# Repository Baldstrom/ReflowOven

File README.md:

# ReflowOven
A reflow oven controller designed in KiCAD, by Jaden Bottemiller

This project is designed to use an STM32 ARM Cortex-M4 microcontroller. 

All onboard devices interface to the microcontroller using I2C (with the exception of the SD Card Slot, which uses SPI). Also has a CAN interface, USB 2.0, and SWD. Features four seven segment displays, three buttons, and a rotary encoder with a custom logic circuit that interfaces with an I2C binary up/down counter to increment, decrement, and maintain accuracy of the relative position of the encoder.

Here is a rendering of the board with all of the parts modelled.
Some models from online resources or default in KiCAD, but many were made by me in Solidworks.

The user interface portion of the board is able to be cut off so that it can be placed anywhere in a mechanical chassis for ease of construction.

Here is the board as seen by default in the KiCAD PCBnew Software.

A PDF of the Schematic Sheets can be found [here](https://github.com/Baldstrom/ReflowOven/blob/main/PDFs/ReflowOven.pdf).

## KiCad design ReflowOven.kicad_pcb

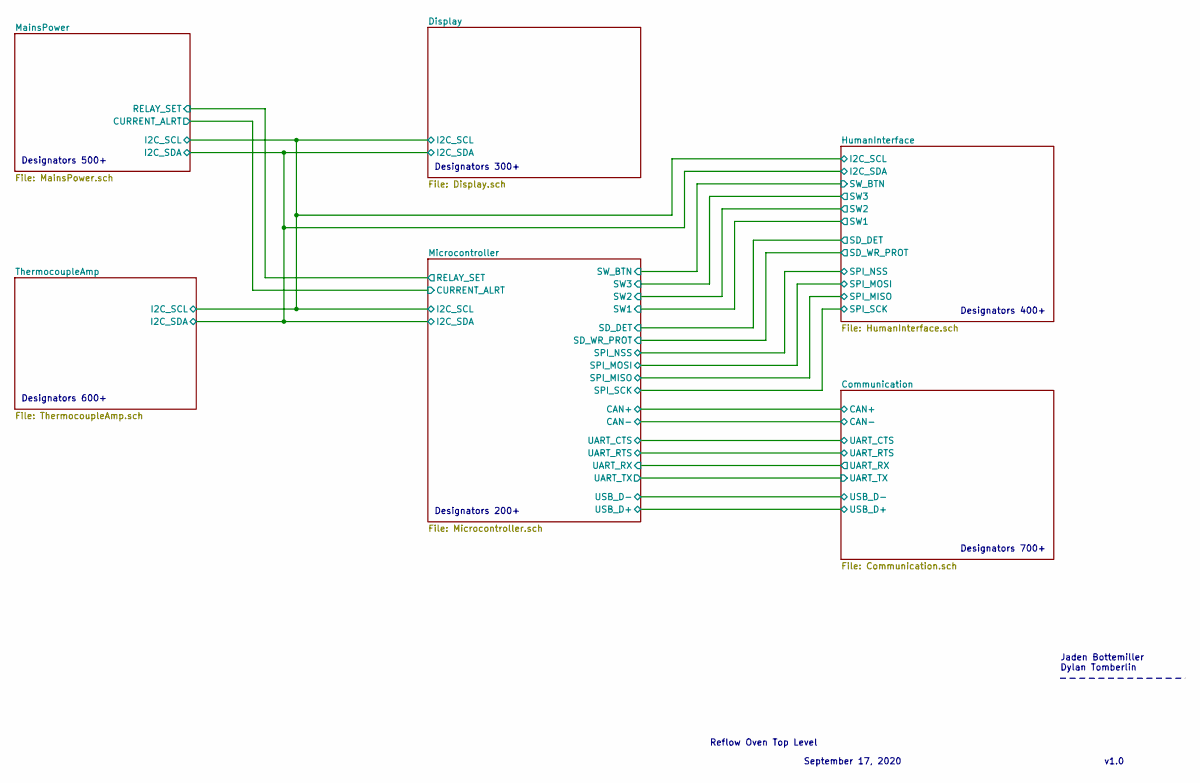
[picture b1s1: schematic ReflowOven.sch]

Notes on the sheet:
Reflow Oven Top Level
v1.0
September 17, 2020
Jaden Bottemiller Dylan Tomberlin
Designators 200+
Designators 600+
Designators 500+
Designators 300+
Designators 400+
Designators 700+

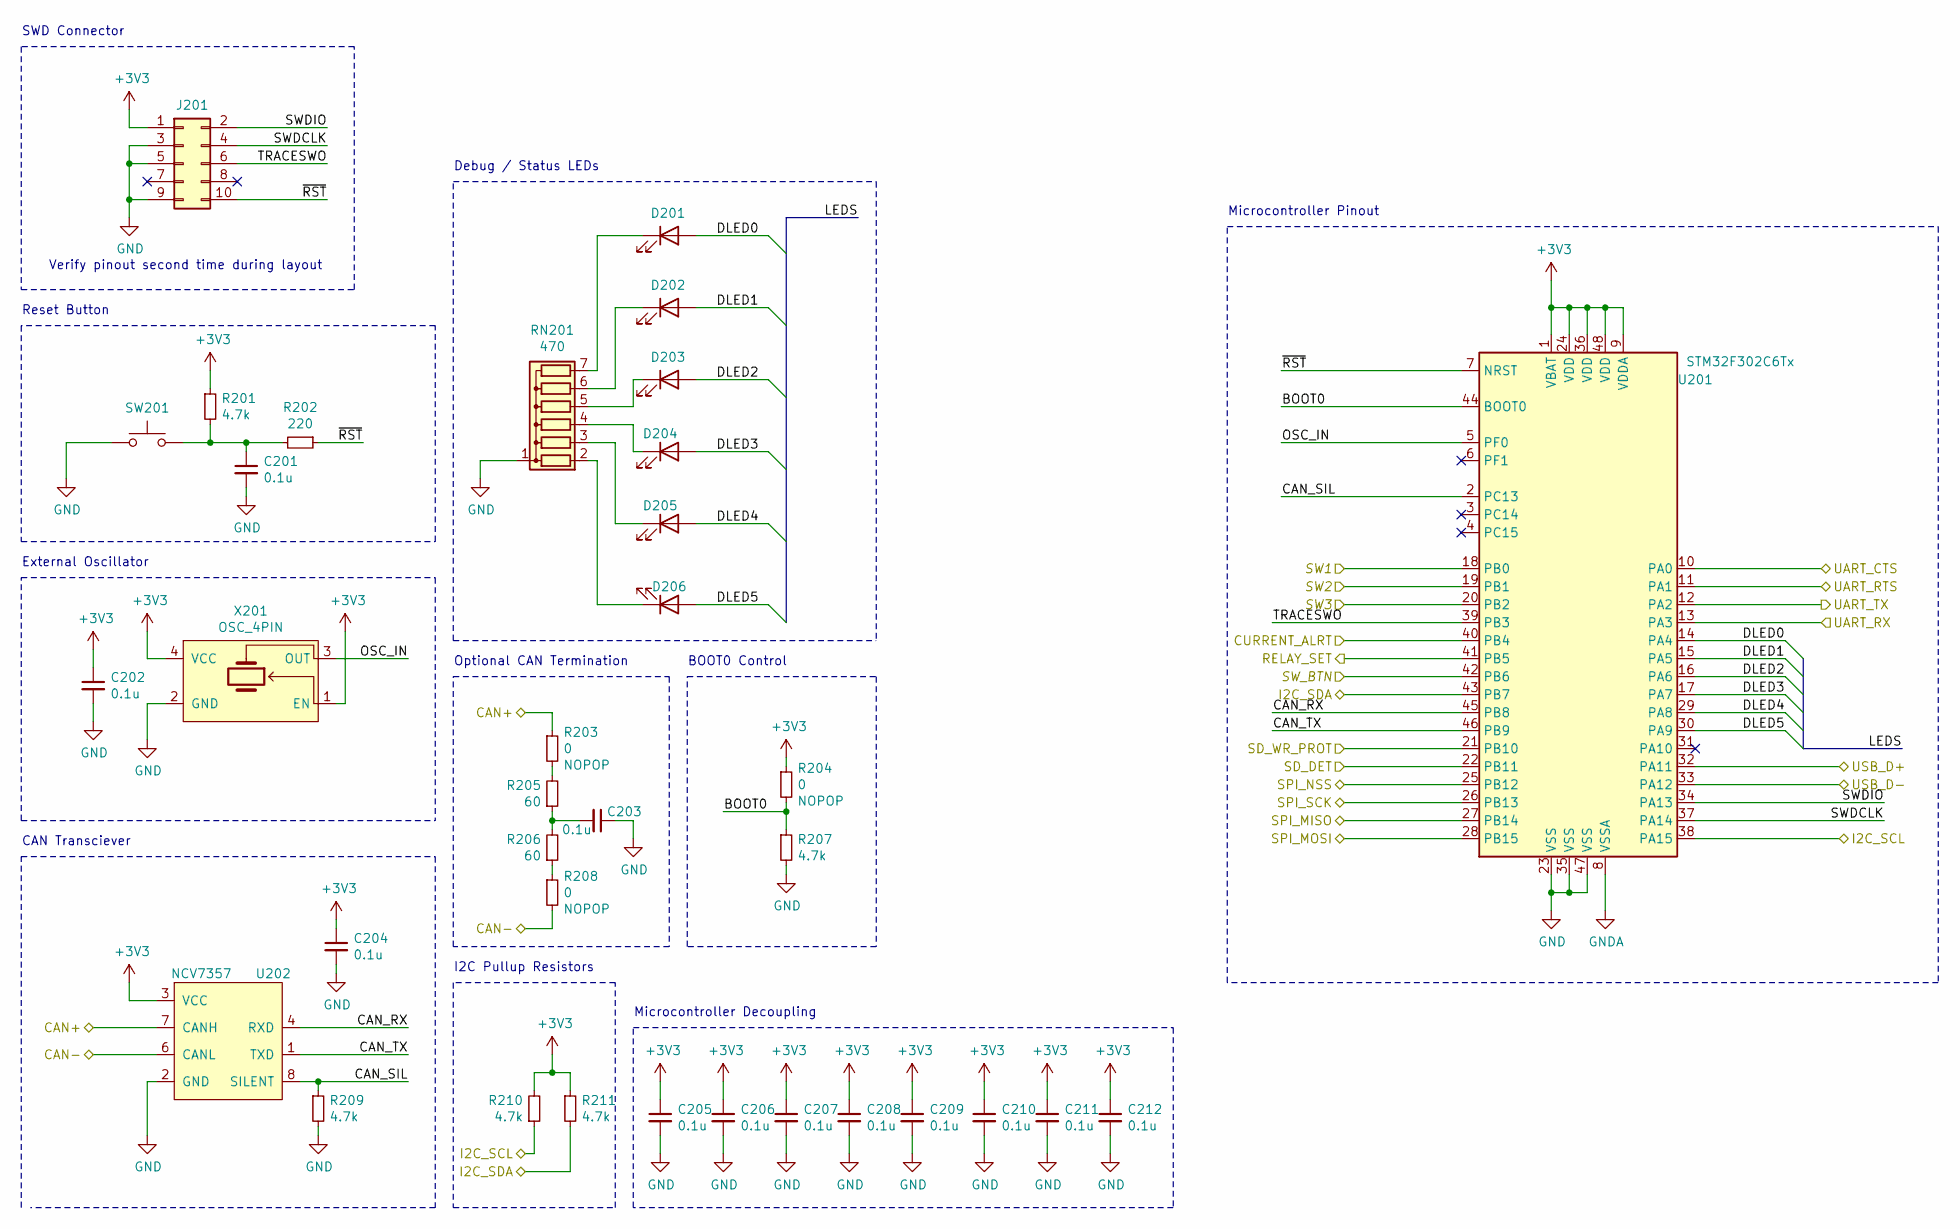
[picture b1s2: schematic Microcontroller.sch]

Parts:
C201, C202, C203, C204, C205, C206, C207, C208, C209, C210, C211, C212: 0.1u; C_0603_1608Metric
D201, D202, D203, D204, D205, D206: LED; LED_0603_1608Metric
J201: Conn_02x05_Odd_Even; CNC_3221-10-0100-00
R201, R207, R209, R210, R211: 4.7k; R_0603_1608Metric
R202: 220; R_0603_1608Metric
R203, R204, R208: 0; R_0201_0603Metric
R205, R206: 60; R_0603_1608Metric
RN201: 470; R_Array_SIP7
SW201: B3U-1100P; SW_B3U-1100P
U201: STM32F302C6Tx; LQFP-48_7x7mm_P0.5mm
U202: NCV7357; SOIC-8_3.9x4.9mm_P1.27mm
X201: OSC_4PIN; KC2016Z48.0000C15XXK

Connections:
/Communication/CAN+: R203.1, U202.7 (CANH); also elsewhere on the board
/Communication/CAN-: R208.2, U202.6 (CANL); also elsewhere on the board
/Communication/UART_CTS: U201.10 (PA0); also elsewhere on the board
/Communication/UART_RTS: U201.11 (PA1); also elsewhere on the board
/Communication/UART_RX: U201.13 (PA3); also elsewhere on the board
/Communication/UART_TX: U201.12 (PA2); also elsewhere on the board
/Communication/USB_D+: U201.32 (PA11); also elsewhere on the board
/Communication/USB_D-: U201.33 (PA12); also elsewhere on the board
/Display/I2C_SCL: R210.1, U201.38 (PA15); also elsewhere on the board
/Display/I2C_SDA: R211.2, U201.43 (PB7); also elsewhere on the board
/HumanInterface/SD_DET: U201.22 (PB11); also elsewhere on the board
/HumanInterface/SD_WR_PROT: U201.21 (PB10); also elsewhere on the board
/HumanInterface/SPI_MISO: U201.27 (PB14); also elsewhere on the board
/HumanInterface/SPI_MOSI: U201.28 (PB15); also elsewhere on the board
/HumanInterface/SPI_NSS: U201.25 (PB12); also elsewhere on the board
/HumanInterface/SPI_SCK: U201.26 (PB13); also elsewhere on the board
/HumanInterface/SW1: U201.18 (PB0); also elsewhere on the board
/HumanInterface/SW2: U201.19 (PB1); also elsewhere on the board
/HumanInterface/SW3: U201.20 (PB2); also elsewhere on the board
/HumanInterface/SW_BTN: U201.42 (PB6); also elsewhere on the board
/MainsPower/CURRENT_ALRT: U201.40 (PB4); also elsewhere on the board
/MainsPower/RELAY_SET: U201.41 (PB5); also elsewhere on the board
/Microcontroller/BOOT0: R204.2, R207.1, U201.44 (BOOT0)
/Microcontroller/CAN_RX: U201.45 (PB8), U202.4 (RXD)
/Microcontroller/CAN_SIL: R209.1, U201.2 (PC13), U202.8 (SILENT)
/Microcontroller/CAN_TX: U201.46 (PB9), U202.1 (TXD)
/Microcontroller/DLED0: D201.2 (A), U201.14 (PA4)
/Microcontroller/DLED1: D202.2 (A), U201.15 (PA5)
/Microcontroller/DLED2: D203.2 (A), U201.16 (PA6)
/Microcontroller/DLED3: D204.2 (A), U201.17 (PA7)
/Microcontroller/DLED4: D205.2 (A), U201.29 (PA8)
/Microcontroller/DLED5: D206.2 (A), U201.30 (PA9)
/Microcontroller/OSC_IN: U201.5 (PF0), X201.3 (OUT)
/Microcontroller/SWDCLK: J201.4, U201.37 (PA14)
/Microcontroller/SWDIO: J201.2, U201.34 (PA13)
/Microcontroller/TRACESWO: J201.6, U201.39 (PB3)
/Microcontroller/~RST: J201.10, R202.1, U201.7 (NRST)
GND: C201.2, C202.2, C203.1, C204.2, C205.2, C206.2, C207.2, C208.2, C209.2, C210.2, C211.2, C212.2, J201.3, J201.5, J201.9, R207.2, R209.2, RN201.1 (common), SW201.1, U201.8 (VSSA), U201.23 (VSS), U201.35 (VSS), U201.47 (VSS), U202.2 (GND), X201.2 (GND); also elsewhere on the board
unnamed: C201.1, R201.2, R202.2, SW201.2
unnamed: C203.2, R205.1, R206.2
unnamed: D201.1 (K), RN201.7 (R6)
unnamed: D202.1 (K), RN201.6 (R5)
unnamed: D203.1 (K), RN201.5 (R4)
unnamed: D204.1 (K), RN201.4 (R3)
unnamed: D205.1 (K), RN201.3 (R2)
unnamed: D206.1 (K), RN201.2 (R1)
unnamed: R203.2, R205.2
unnamed: R206.1, R208.1

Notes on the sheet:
Microcontroller Decoupling
Microcontroller Pinout
CAN Transciever
I2C Pullup Resistors
External Oscillator
Verify pinout second time during layout
SWD Connector
Reset Button
BOOT0 Control
Optional CAN Termination
Debug / Status LEDs

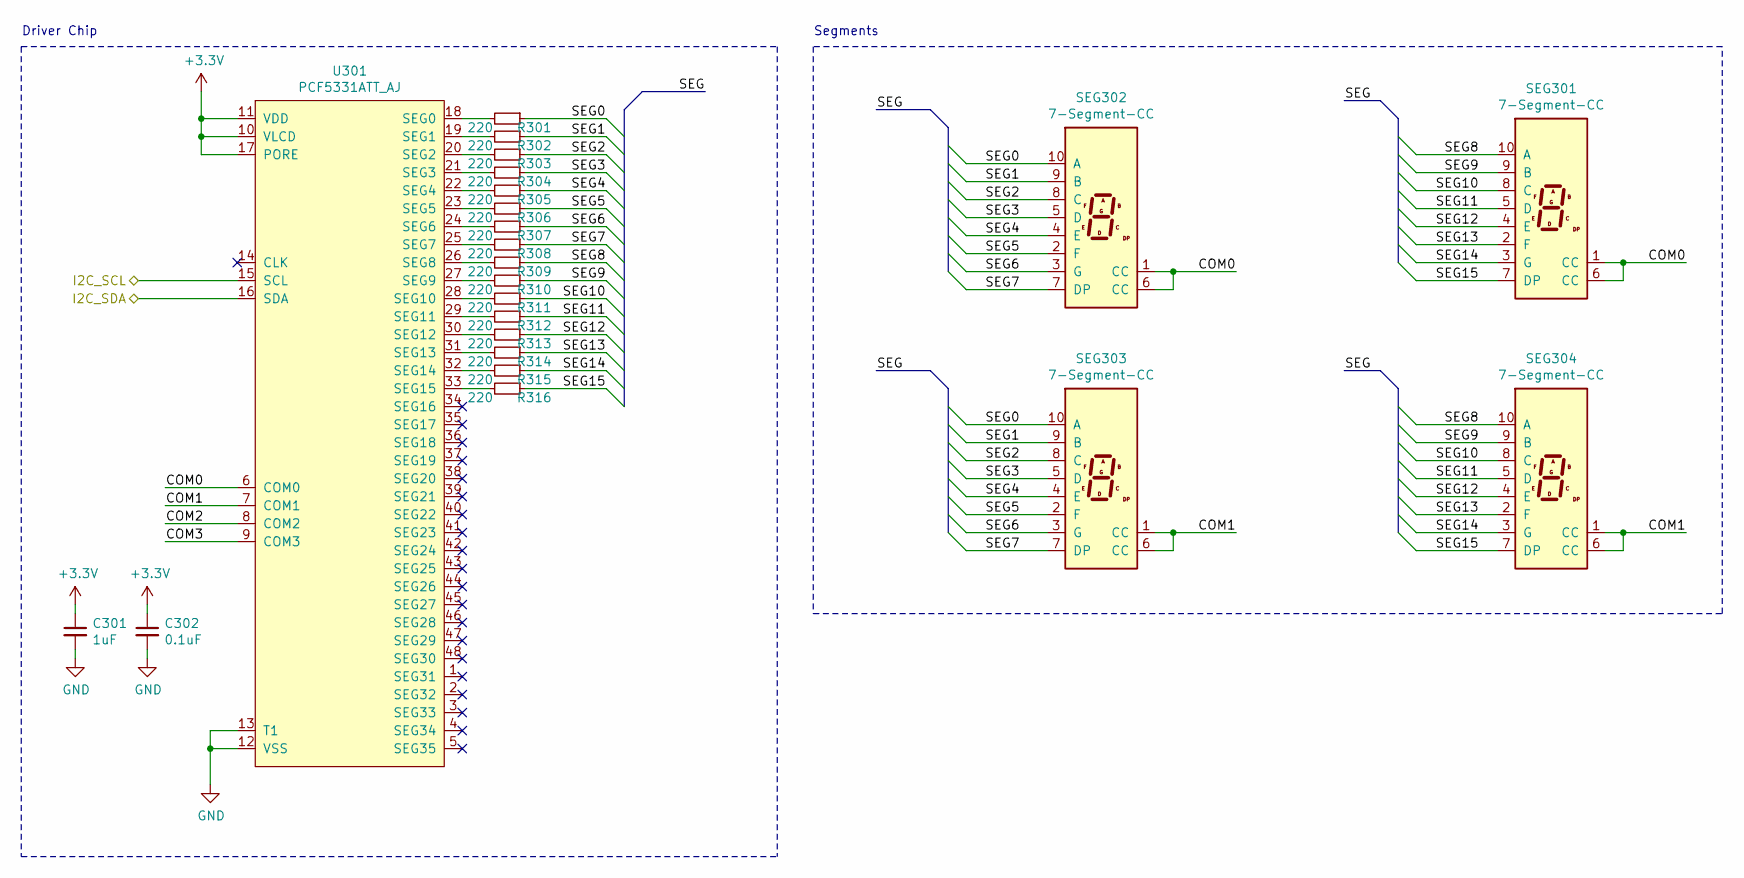
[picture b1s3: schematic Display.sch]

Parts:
C301: 1uF; C_0603_1608Metric
C302: 0.1uF; C_0603_1608Metric
R301, R302, R303, R304, R305, R306, R307, R308, R309, R310, R311, R312, R313, R314, R315, R316: 220; R_0603_1608Metric
SEG301, SEG302, SEG303, SEG304: 7-Segment-CC; Sx39-1xxxxx
U301: PCF5331ATT_AJ; TSSOP-48_6.1x12.5mm_P0.5mm

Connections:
/Display/COM0: SEG301.1 (CC), SEG301.6 (CC), SEG302.1 (CC), SEG302.6 (CC), U301.6 (COM0)
/Display/COM1: SEG303.1 (CC), SEG303.6 (CC), SEG304.1 (CC), SEG304.6 (CC), U301.7 (COM1)
/Display/COM2: U301.8 (COM2)
/Display/COM3: U301.9 (COM3)
/Display/I2C_SCL: U301.15 (SCL); also elsewhere on the board
/Display/I2C_SDA: U301.16 (SDA); also elsewhere on the board
/Display/SEG0: R301.1, SEG302.10 (A), SEG303.10 (A)
/Display/SEG1: R302.1, SEG302.9 (B), SEG303.9 (B)
/Display/SEG2: R303.1, SEG302.8 (C), SEG303.8 (C)
/Display/SEG3: R304.1, SEG302.5 (D), SEG303.5 (D)
/Display/SEG4: R305.1, SEG302.4 (E), SEG303.4 (E)
/Display/SEG5: R306.1, SEG302.2 (F), SEG303.2 (F)
/Display/SEG6: R307.1, SEG302.3 (G), SEG303.3 (G)
/Display/SEG7: R308.1, SEG302.7 (DP), SEG303.7 (DP)
/Display/SEG8: R309.1, SEG301.10 (A), SEG304.10 (A)
/Display/SEG9: R310.1, SEG301.9 (B), SEG304.9 (B)
/Display/SEG10: R311.1, SEG301.8 (C), SEG304.8 (C)
/Display/SEG11: R312.1, SEG301.5 (D), SEG304.5 (D)
/Display/SEG12: R313.1, SEG301.4 (E), SEG304.4 (E)
/Display/SEG13: R314.1, SEG301.2 (F), SEG304.2 (F)
/Display/SEG14: R315.1, SEG301.3 (G), SEG304.3 (G)
/Display/SEG15: R316.1, SEG301.7 (DP), SEG304.7 (DP)
GND: C301.2, C302.2, U301.12 (VSS), U301.13 (T1); also elsewhere on the board
unnamed: R301.2, U301.18 (SEG0)
unnamed: R302.2, U301.19 (SEG1)
unnamed: R303.2, U301.20 (SEG2)
unnamed: R304.2, U301.21 (SEG3)
unnamed: R305.2, U301.22 (SEG4)
unnamed: R306.2, U301.23 (SEG5)
unnamed: R307.2, U301.24 (SEG6)
unnamed: R308.2, U301.25 (SEG7)
unnamed: R309.2, U301.26 (SEG8)
unnamed: R310.2, U301.27 (SEG9)
unnamed: R311.2, U301.28 (SEG10)
unnamed: R312.2, U301.29 (SEG11)
unnamed: R313.2, U301.30 (SEG12)
unnamed: R314.2, U301.31 (SEG13)
unnamed: R315.2, U301.32 (SEG14)
unnamed: R316.2, U301.33 (SEG15)

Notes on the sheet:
Driver Chip
Segments

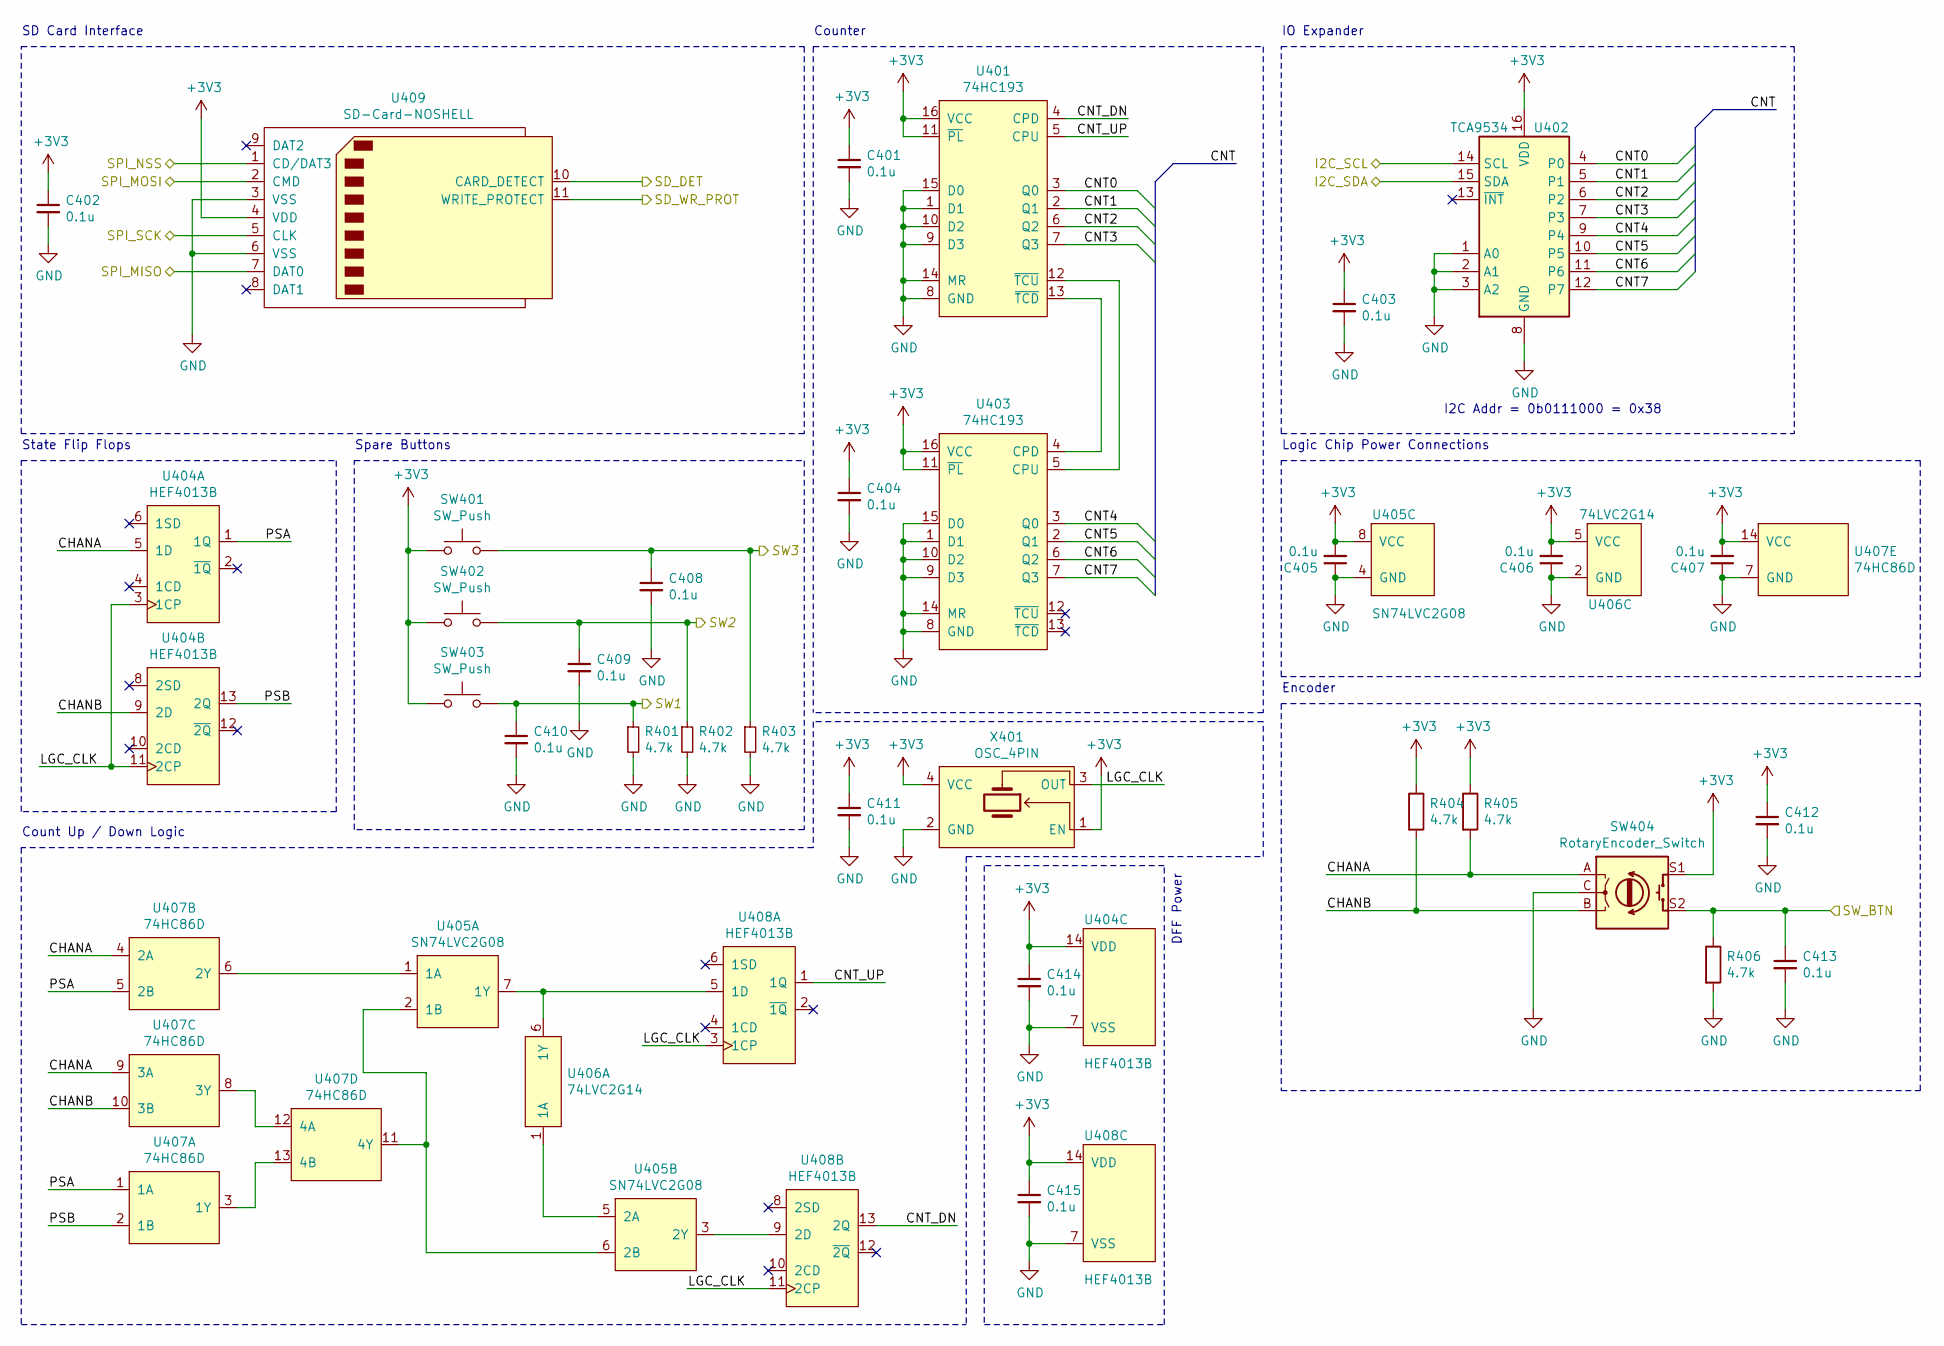
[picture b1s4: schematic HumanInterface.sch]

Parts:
C401, C402, C403, C404, C405, C406, C407, C408, C409, C410, C411, C412, C413, C414, C415: 0.1u; C_0603_1608Metric
R401, R402, R403, R404, R405, R406: 4.7k; R_0603_1608Metric
SW401, SW402, SW403: SW_Push; SW_KS11R21CQD
SW404: RotaryEncoder_Switch; EN12-HS22AF20
U401, U403: 74HC193; SOIC-16_3.9x9.9mm_P1.27mm
U402: TCA9534; TSSOP-16_4.4x5mm_P0.65mm
U404, U408: HEF4013B; SOIC-14_3.9x8.7mm_P1.27mm
U405: SN74LVC2G08; VSSOP-8_2.3x2mm_P0.5mm
U406: 74LVC2G14; TSOP-6_1.65x3.05mm_P0.95mm
U407: 74HC86D; SOIC-14_3.9x8.7mm_P1.27mm
U409: SD-Card-NOSHELL; AMPHENOL-10067847
X401: OSC_4PIN; KC2016Z48.0000C15XXK

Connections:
/Display/I2C_SCL: U402.14 (SCL); also elsewhere on the board
/Display/I2C_SDA: U402.15 (SDA); also elsewhere on the board
/HumanInterface/CHANA: R405.2, SW404.A, U404.5 (1D), U407.4 (2A), U407.9 (3A)
/HumanInterface/CHANB: R404.2, SW404.B, U404.9 (2D), U407.10 (3B)
/HumanInterface/CNT0: U401.3 (Q0), U402.4 (P0)
/HumanInterface/CNT1: U401.2 (Q1), U402.5 (P1)
/HumanInterface/CNT2: U401.6 (Q2), U402.6 (P2)
/HumanInterface/CNT3: U401.7 (Q3), U402.7 (P3)
/HumanInterface/CNT4: U402.9 (P4), U403.3 (Q0)
/HumanInterface/CNT5: U402.10 (P5), U403.2 (Q1)
/HumanInterface/CNT6: U402.11 (P6), U403.6 (Q2)
/HumanInterface/CNT7: U402.12 (P7), U403.7 (Q3)
/HumanInterface/CNT_DN: U401.4 (CPD), U408.13 (2Q)
/HumanInterface/CNT_UP: U401.5 (CPU), U408.1 (1Q)
/HumanInterface/LGC_CLK: U404.3 (1CP), U404.11 (2CP), U408.3 (1CP), U408.11 (2CP), X401.3 (OUT)
/HumanInterface/PSA: U404.1 (1Q), U407.1 (1A), U407.5 (2B)
/HumanInterface/PSB: U404.13 (2Q), U407.2 (1B)
/HumanInterface/SD_DET: U409.10 (CARD_DETECT); also elsewhere on the board
/HumanInterface/SD_WR_PROT: U409.11 (WRITE_PROTECT); also elsewhere on the board
/HumanInterface/SPI_MISO: U409.7 (DAT0); also elsewhere on the board
/HumanInterface/SPI_MOSI: U409.2 (CMD); also elsewhere on the board
/HumanInterface/SPI_NSS: U409.1 (CD/DAT3); also elsewhere on the board
/HumanInterface/SPI_SCK: U409.5 (CLK); also elsewhere on the board
/HumanInterface/SW1: C410.1, R401.1, SW403.2; also elsewhere on the board
/HumanInterface/SW2: C409.1, R402.1, SW402.2; also elsewhere on the board
/HumanInterface/SW3: C408.1, R403.1, SW401.2; also elsewhere on the board
/HumanInterface/SW_BTN: C413.1, R406.1, SW404.S2; also elsewhere on the board
GND: C401.2, C402.2, C403.2, C404.2, C405.1, C406.1, C407.1, C408.2, C409.2, C410.2, C411.2, C412.2, C413.2, C414.2, C415.2, R401.2, R402.2, R403.2, R406.2, SW404.C, U401.1 (D1), U401.8 (GND), U401.9 (D3), U401.10 (D2), U401.14 (MR), U401.15 (D0), U402.1 (A0), U402.2 (A1), U402.3 (A2), U402.8 (GND), U403.1 (D1), U403.8 (GND), U403.9 (D3), U403.10 (D2), U403.14 (MR), U403.15 (D0), U404.7 (VSS), U405.4 (GND), U406.2 (GND), U407.7 (GND), U408.7 (VSS), U409.3 (VSS), U409.6 (VSS), U409.GND, X401.2 (GND); also elsewhere on the board
unnamed: U401.12 (~TCU), U403.5 (CPU)
unnamed: U401.13 (~TCD), U403.4 (CPD)
unnamed: U405.1 (1A), U407.6 (2Y)
unnamed: U405.2 (1B), U405.6 (2B), U407.11 (4Y)
unnamed: U405.3 (2Y), U408.9 (2D)
unnamed: U405.5 (2A), U406.1 (1A)
unnamed: U405.7 (1Y), U406.6 (1Y), U408.5 (1D)
unnamed: U407.8 (3Y), U407.12 (4A)
unnamed: U407.3 (1Y), U407.13 (4B)

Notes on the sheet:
SD Card Interface
Encoder
Counter
State Flip Flops
Count Up / Down Logic
Logic Chip Power Connections
IO Expander
Spare Buttons
I2C Addr = 0b0111000 = 0x38
DFF Power

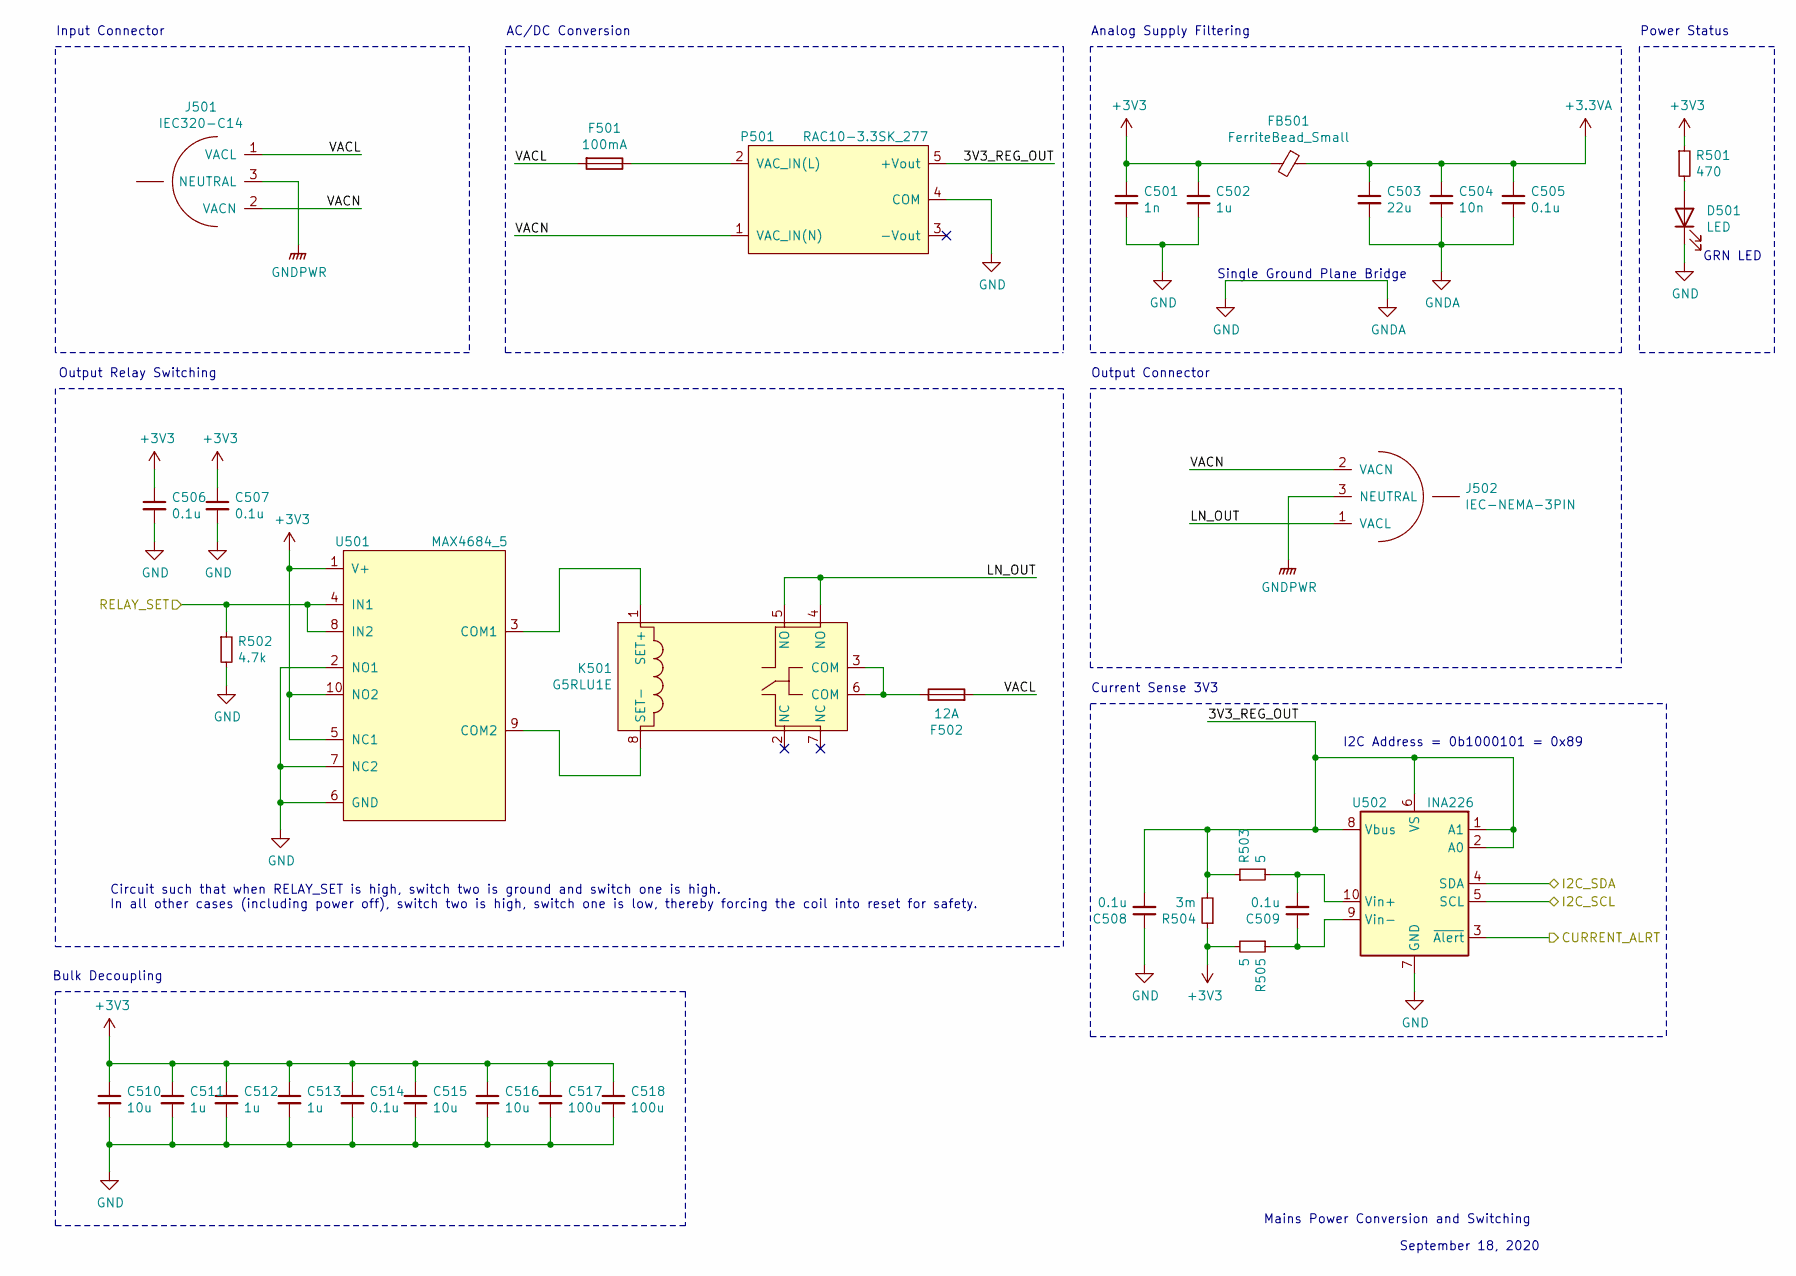
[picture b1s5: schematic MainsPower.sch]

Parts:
C501: 1n; C_0603_1608Metric
C502, C511, C512, C513: 1u; C_0603_1608Metric
C503: 22u; C_0603_1608Metric
C504: 10n; C_0603_1608Metric
C505, C506, C507, C508, C509, C514: 0.1u; C_0603_1608Metric
C510, C515, C516: 10u; C_0603_1608Metric
C517, C518: 100u; CP_Radial_D5.0mm_P2.00mm
D501: LED; LED_0603_1608Metric
F501: 100mA; FUSC6125X279N
F502: 12A; FUSC6125X279N
FB501: FerriteBead_Small; L_0603_1608Metric
J501: IEC320-C14; 3x1-0.24in-Spade-SMD
J502: IEC-NEMA-3PIN; 3x1-0.24in-Spade-SMD
K501: G5RLU1E; G5RLU-1-E DC3
P501: RAC10-3.3SK_277; RAC10-3.3SK-277
R501: 470; R_0603_1608Metric
R502: 4.7k; R_0603_1608Metric
R503, R505: 5; R_0603_1608Metric
R504: 3m; R_0805_2012Metric
U501: MAX4684_5; MSOP-10_3x3mm_P0.5mm
U502: INA226; MSOP-10_3x3mm_P0.5mm

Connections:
+3.3VA: C503.1, C504.1, C505.1, FB501.1; also elsewhere on the board
/Display/I2C_SCL: U502.5 (SCL); also elsewhere on the board
/Display/I2C_SDA: U502.4 (SDA); also elsewhere on the board
/MainsPower/3V3_REG_OUT: C508.2, P501.5 (+Vout), R503.1, R504.2, U502.1 (A1), U502.2 (A0), U502.6 (VS), U502.8 (Vbus)
/MainsPower/CURRENT_ALRT: U502.3 (~Alert~); also elsewhere on the board
/MainsPower/LN_OUT: J502.1 (VACL), K501.4 (NO), K501.5 (NO)
/MainsPower/RELAY_SET: R502.1, U501.4 (IN1), U501.8 (IN2); also elsewhere on the board
/MainsPower/VACL: F501.2, F502.2, J501.1 (VACL)
/MainsPower/VACN: J501.2 (VACN), J502.2 (VACN), P501.1 (VAC_IN(N))
GND: C501.2, C502.2, C503.2, C504.2, C505.2, C506.2, C507.2, C508.1, C510.2, C511.2, C512.2, C513.2, C514.2, C515.2, C516.2, C517.2, C518.2, D501.1 (K), P501.4 (COM), R502.2, U501.2 (NO1), U501.6 (GND), U501.7 (NC2), U502.7 (GND); also elsewhere on the board
GNDPWR: J501.3 (NEUTRAL), J502.3 (NEUTRAL)
unnamed: C509.1, R505.1, U502.9 (Vin-)
unnamed: C509.2, R503.2, U502.10 (Vin+)
unnamed: D501.2 (A), R501.2
unnamed: F501.1, P501.2 (VAC_IN(L))
unnamed: F502.1, K501.3 (COM), K501.6 (COM)
unnamed: K501.1 (SET+), U501.3 (COM1)
unnamed: K501.8 (SET-), U501.9 (COM2)

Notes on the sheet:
Bulk Decoupling
AC/DC Conversion
Mains Power Conversion and Switching
September 18, 2020
Circuit such that when RELAY_SET is high, switch two is ground and switch one is high. In all other cases (including power off), switch two is high, switch one is low, thereby forcing the coil into reset for safety.
Output Relay Switching
Input Connector
Output Connector
Analog Supply Filtering
Single Ground Plane Bridge
Current Sense 3V3
I2C Address = 0b1000101 = 0x89
GRN LED
Power Status

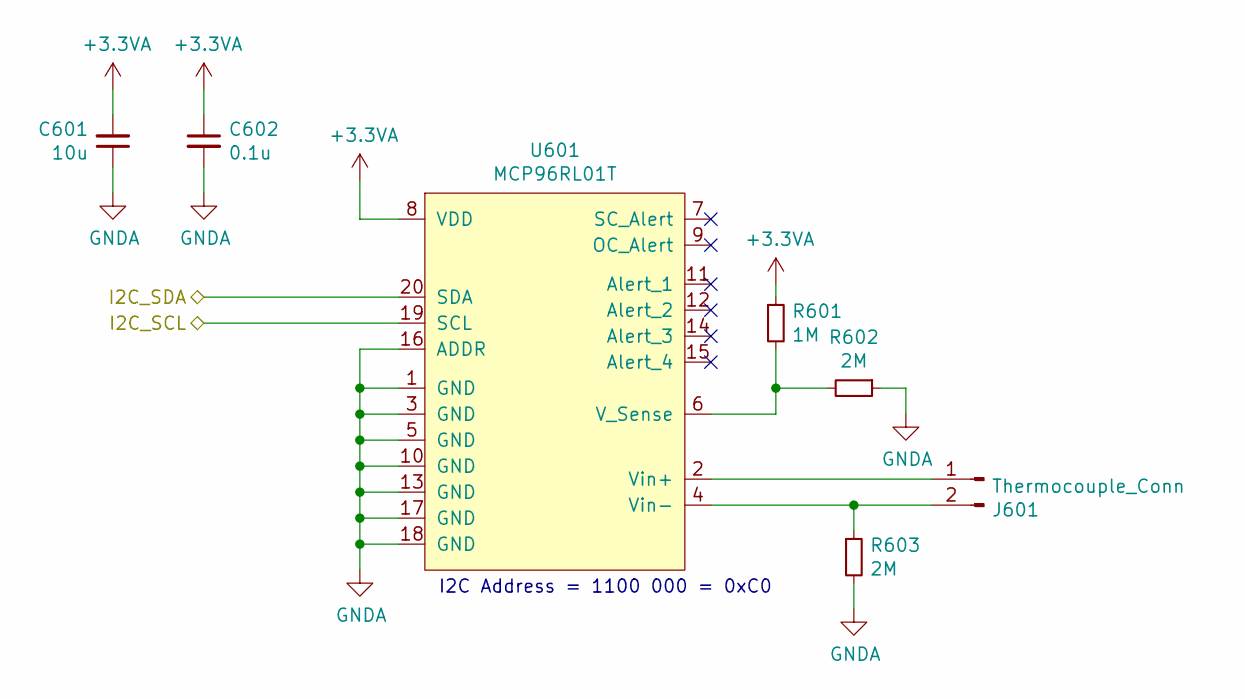
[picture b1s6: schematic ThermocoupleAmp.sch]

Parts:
C601: 10u; C_0603_1608Metric
C602: 0.1u; C_0603_1608Metric
J601: Thermocouple_Conn; PRT-13612
R601: 1M; R_0603_1608Metric
R602, R603: 2M; R_0603_1608Metric
U601: MCP96RL01T; QFN-20_EP_5x5_Pitch0.65mm

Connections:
+3.3VA: C601.2, C602.1, R601.1, U601.8 (VDD); also elsewhere on the board
/Display/I2C_SCL: U601.19 (SCL); also elsewhere on the board
/Display/I2C_SDA: U601.20 (SDA); also elsewhere on the board
GND: C601.1, C602.2, R602.1, R603.2, U601.1 (GND), U601.3 (GND), U601.5 (GND), U601.10 (GND), U601.13 (GND), U601.16 (ADDR), U601.17 (GND), U601.18 (GND); also elsewhere on the board
unnamed: J601.1, U601.2 (Vin+)
unnamed: J601.2, R603.1, U601.4 (Vin-)
unnamed: R601.2, R602.2, U601.6 (V_Sense)

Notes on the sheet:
I2C Address = 1100 000 = 0xC0

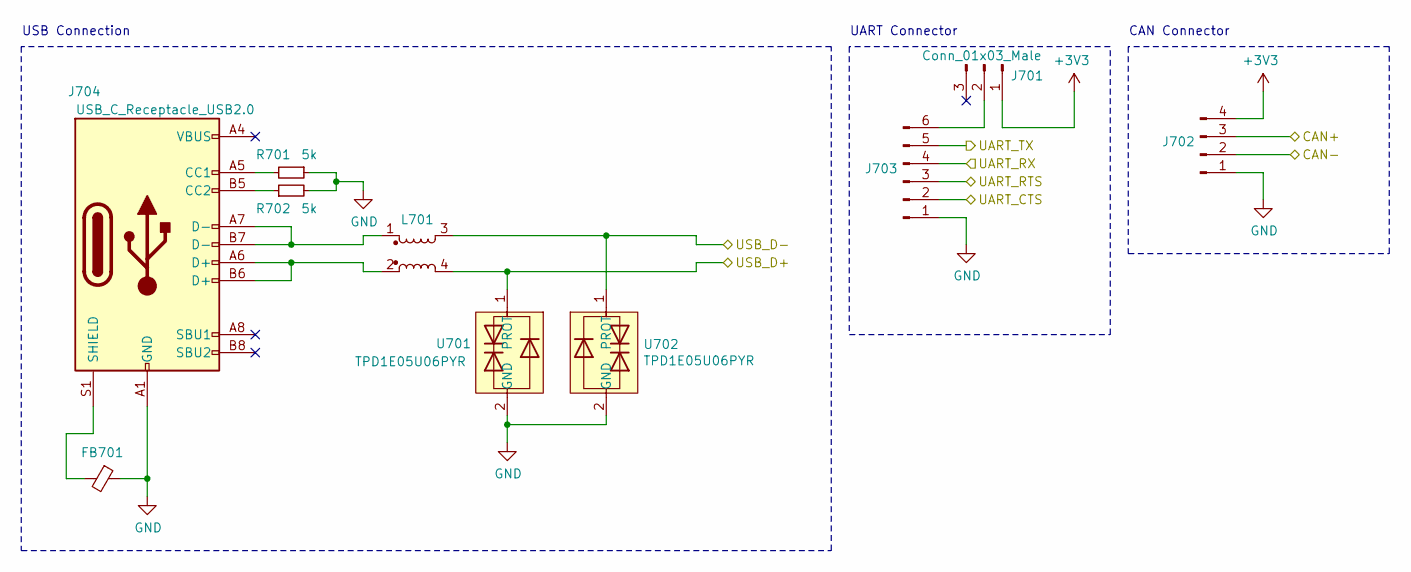
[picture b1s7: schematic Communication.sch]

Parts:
FB701: FerriteBead_Small; L_0603_1608Metric
J701: Conn_01x03_Male; PinHeader_1x03_P1.00mm_Vertical
J702: Microfit-4pin; PinHeader_2x02_P1.00mm_Vertical
J703: Conn_01x06_Male; PinHeader_1x06_P1.00mm_Vertical
J704: USB_C_Receptacle_USB2.0; USB_C_Receptacle_Amphenol_12401610E4-2A
L701: L_Coupled_Small_1324; 744231091
R701, R702: 5k; R_0603_1608Metric
U701, U702: TPD1E05U06PYR; D_0402_1005Metric

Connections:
/Communication/CAN+: J702.3; also elsewhere on the board
/Communication/CAN-: J702.2; also elsewhere on the board
/Communication/UART_CTS: J703.2; also elsewhere on the board
/Communication/UART_RTS: J703.3; also elsewhere on the board
/Communication/UART_RX: J703.4; also elsewhere on the board
/Communication/UART_TX: J703.5; also elsewhere on the board
/Communication/USB_D+: L701.4, U701.1 (PROT); also elsewhere on the board
/Communication/USB_D-: L701.3, U702.1 (PROT); also elsewhere on the board
GND: FB701.1, J702.1, J703.1, J704.A1 (GND), J704.A12 (GND), J704.B1 (GND), J704.B12 (GND), R701.1, R702.2, U701.2 (GND), U702.2 (GND); also elsewhere on the board
unnamed: FB701.2, J704.S1 (SHIELD)
unnamed: J701.2, J703.6
unnamed: J704.A4 (VBUS), J704.A9 (VBUS), J704.B4 (VBUS), J704.B9 (VBUS)
unnamed: J704.A5 (CC1), R701.2
unnamed: J704.A6 (D+), J704.B6 (D+), L701.2
unnamed: J704.A7 (D-), J704.B7 (D-), L701.1
unnamed: J704.B5 (CC2), R702.1

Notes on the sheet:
USB Connection
UART Connector
CAN Connector

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
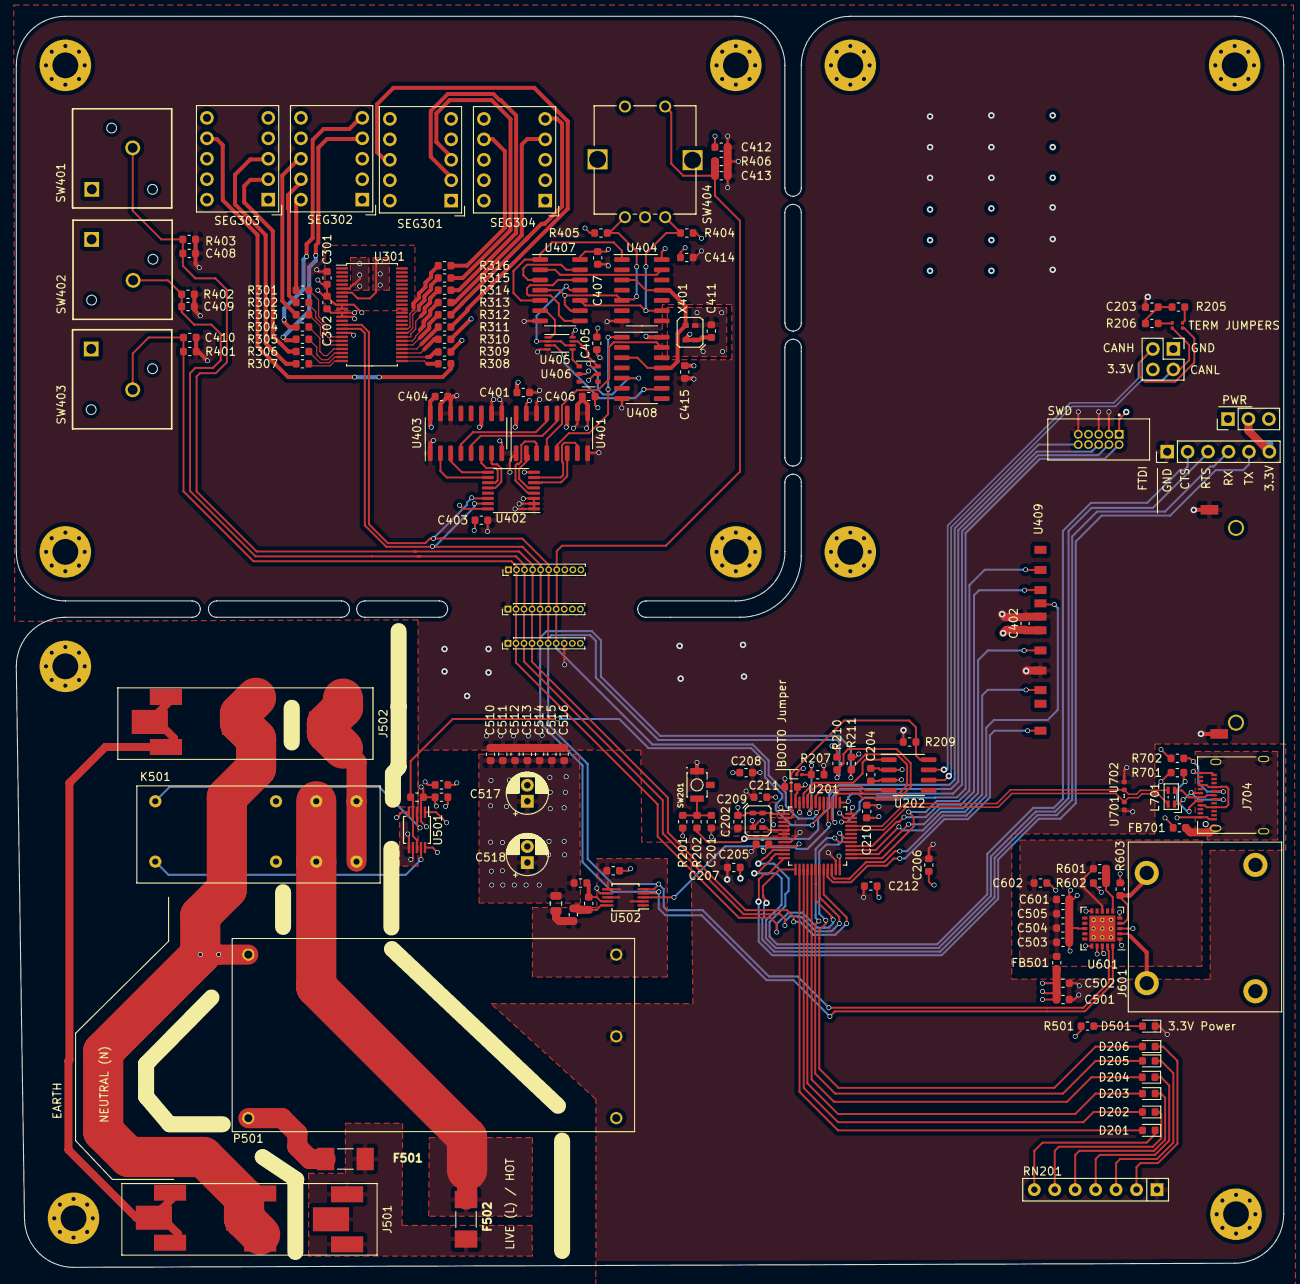
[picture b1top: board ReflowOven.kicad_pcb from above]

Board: 4 copper layers, 157.5 x 155.4 mm, 143 parts (0 on the bottom side), 130 nets.

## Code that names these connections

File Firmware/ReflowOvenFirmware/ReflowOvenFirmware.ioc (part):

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Mcu.Name=STM32F302C(B-C)Tx
Mcu.Package=LQFP48
Mcu.UserName=STM32F302CBTx
PA0.Mode=CTS_RTS
PA0.Signal=USART2_CTS
PA1.Mode=CTS_RTS
PA1.Signal=USART2_RTS
PA11.Mode=Device
PA11.Signal=USB_DM
PA12.Mode=Device
PA12.Signal=USB_DP
PA13.Mode=Trace_Asynchronous_SW
PA13.Signal=SYS_JTMS-SWDIO
PA14.Mode=Trace_Asynchronous_SW
PA14.Signal=SYS_JTCK-SWCLK
PA15.Mode=SMBus-two-wire-Interface
PA15.Signal=I2C1_SCL
PA2.Mode=Asynchronous
PA2.Signal=USART2_TX
PA3.Mode=Asynchronous
PA3.Signal=USART2_RX
PA4.GPIOParameters=GPIO_Label
PA4.GPIO_Label=DLED0
PA4.Signal=GPIO_Output
PA5.GPIOParameters=GPIO_Label
PA5.GPIO_Label=DLED1
PA5.Signal=GPIO_Output
PA6.GPIOParameters=GPIO_Label
PA6.GPIO_Label=DLED2
PA6.Signal=GPIO_Output
PA7.GPIOParameters=GPIO_Label
PA7.GPIO_Label=DLED3
PA7.Signal=GPIO_Output
PA8.GPIOParameters=GPIO_Label
PA8.GPIO_Label=DLED4
PA8.Signal=GPIO_Output
PA9.GPIOParameters=GPIO_Label
PA9.GPIO_Label=DLED5
PA9.Signal=GPIO_Output
PB0.GPIOParameters=GPIO_Label
PB0.GPIO_Label=SW1
PB0.Signal=GPIO_Input
PB1.GPIOParameters=GPIO_Label
PB1.GPIO_Label=SW2
PB1.Signal=GPIO_Input
PB10.GPIOParameters=GPIO_Label
PB10.GPIO_Label=SD_WR_PROT
PB10.Signal=GPIO_Input
PB11.GPIOParameters=GPIO_Label
PB11.GPIO_Label=SD_DET
PB11.Signal=GPIO_Input
PB12.Mode=NSS_Signal_Hard_Output
PB12.Signal=SPI2_NSS
PB13.Mode=Full_Duplex_Master
PB13.Signal=SPI2_SCK
PB14.Mode=Full_Duplex_Master
PB14.Signal=SPI2_MISO
PB15.Mode=Full_Duplex_Master
PB15.Signal=SPI2_MOSI
PB2.GPIOParameters=GPIO_Label
PB2.GPIO_Label=SW3
PB2.Signal=GPIO_Input
PB3.Mode=Trace_Asynchronous_SW
PB3.Signal=SYS_JTDO-TRACESWO
PB4.GPIOParameters=GPIO_Label
PB4.GPIO_Label=CURRENT_ALRT
PB4.Signal=GPIO_Input
PB5.GPIOParameters=GPIO_Label
PB5.GPIO_Label=RELAY_SET
PB5.Signal=GPIO_Output
PB6.GPIOParameters=GPIO_Label
PB6.GPIO_Label=ENC_SW
PB6.Signal=GPIO_Input
PB7.Mode=SMBus-two-wire-Interface
PB7.Signal=I2C1_SDA
PB8.Mode=Master
PB8.Signal=CAN_RX
PB9.Mode=Master
PB9.Signal=CAN_TX
PC13.GPIOParameters=GPIO_Label
PC13.GPIO_Label=CAN_SIL
PC13.Signal=GPIO_Output
PF0-OSC_IN.Mode=HSE-External-Clock-Source
PF0-OSC_IN.Signal=RCC_OSC_IN
RCC.HSEPLLFreq_Value=16000000
RCC.HSE_VALUE=32000000
RCC.SYSCLKFreq_VALUE=48000000
RCC.SYSCLKSourceVirtual=RCC_SYSCLKSOURCE_PLLCLK
board=custom

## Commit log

2020-10-26 Initial commit, no firmware
2020-10-26 Updated Repo
2020-11-11 Pushed firmware

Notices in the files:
parts and their libraries:
Copyright 2016 Accelerated Designs. All rights reserved.
